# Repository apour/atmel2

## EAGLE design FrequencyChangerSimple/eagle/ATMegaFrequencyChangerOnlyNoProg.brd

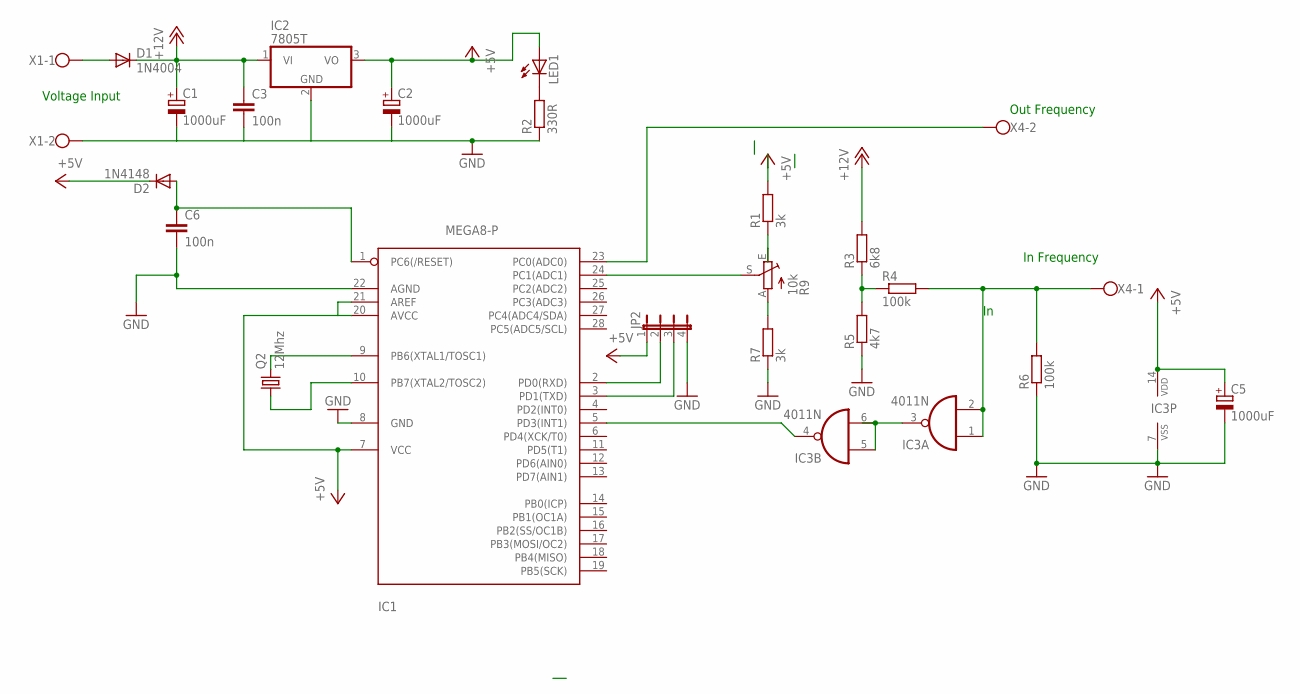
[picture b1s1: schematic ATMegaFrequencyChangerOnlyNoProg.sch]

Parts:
C1, C2, C5: 1000uF; E2,5-7
C3, C6: 100n; C025-024X044
D1: 1N4004; DO41-10
D2: 1N4148; DO35-10
IC1: MEGA8-P; DIL28-3
IC2: 7805T; TO220H
IC3: 4011N; DIL14
JP2: JP4E; JP4
LED1: LED5MM
Q2: 12Mhz; HC18U-V
R1, R7: 3k; 0207/10
R2: 330R; 0204/5
R3: 6k8; 0207/10
R4, R6: 100k; 0207/10
R5: 4k7; 0207/10
R9: 10k; RS3
X1, X4: W237-02P; W237-132

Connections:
+5V: C2.+, C5.+, D2.C, IC1.7 (VCC), IC1.20 (AVCC), IC1.21 (AREF), IC2.3 (VO), IC3.14 (VDD), JP2.1, LED1.A, R1.2
+12V: C1.+, C3.1, D1.C, IC2.1 (VI), R3.2
GND: C5.-, IC3.7 (VSS), R6.1
unnamed: D1.A, X1.1
unnamed: IC1.23 (PC0(ADC0)), X4.2
unnamed: IC1.5 (PD3(INT1)), IC3.4 (O)
unnamed: R3.1, R4.1, R5.2
unnamed: IC3.3 (O), IC3.5 (I0), IC3.6 (I1)
unnamed: R1.1, R9.E
unnamed: IC1.9 (PB6(XTAL1/TOSC1)), Q2.2
unnamed: R7.2, R9.A
unnamed: IC1.2 (PD0(RXD)), JP2.2
unnamed: IC1.24 (PC1(ADC1)), R9.S
unnamed: IC1.10 (PB7(XTAL2/TOSC2)), Q2.1
unnamed: IC1.3 (PD1(TXD)), JP2.3
unnamed: IC3.1 (I0), IC3.2 (I1), R4.2, R6.2, X4.1
unnamed: C1.-, C2.-, C3.2, C6.2, IC1.8 (GND), IC1.22 (AGND), IC2.2 (GND), JP2.4, R2.1, R5.1, R7.1, X1.2
unnamed: C6.1, D2.A, IC1.1 (PC6(/RESET))
unnamed: LED1.K (C), R2.2

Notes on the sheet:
Voltage Input
Out Frequency
In Frequency

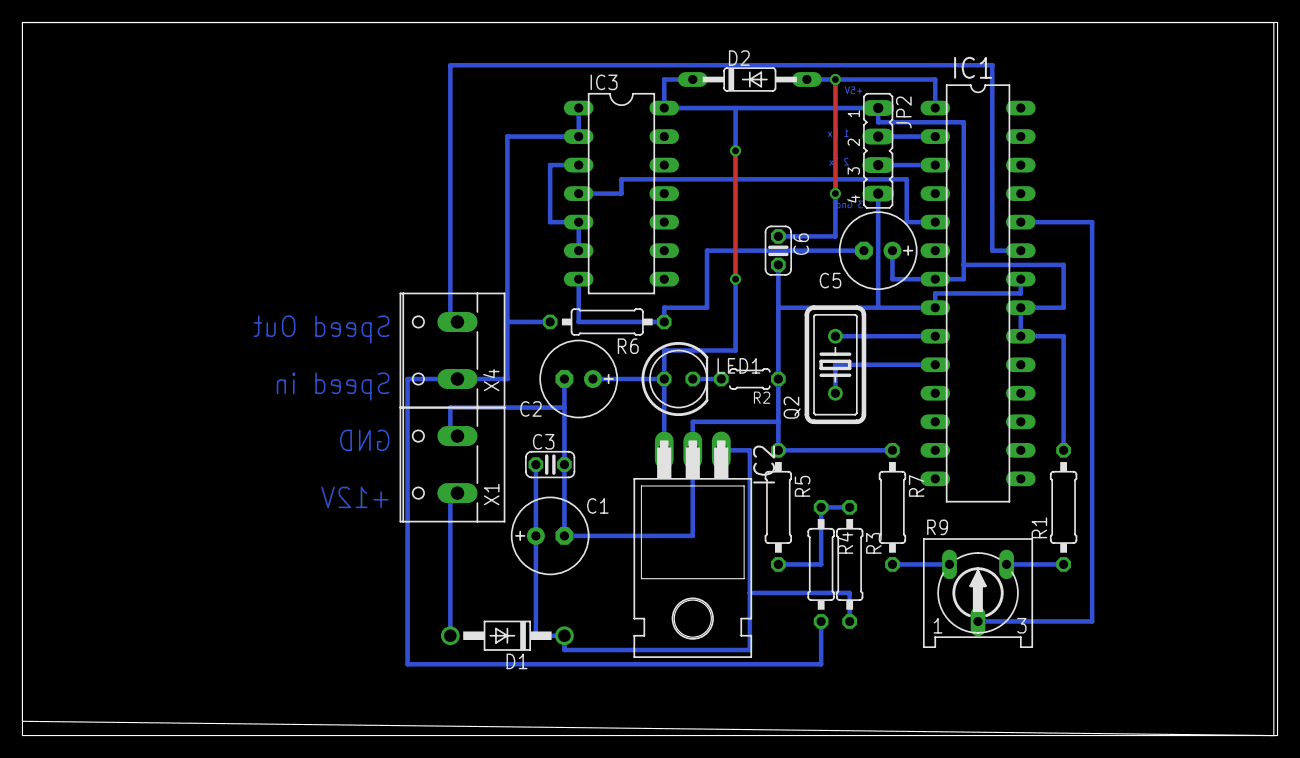
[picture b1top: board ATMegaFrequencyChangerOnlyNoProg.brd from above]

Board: 2 copper layers, 111.8 x 63.5 mm, 23 parts (0 on the bottom side), 19 nets.

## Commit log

2023-01-18 Tested in car Roman
2023-01-18 Scheme and board from eagle
2023-01-18 add projects
2023-02-27 add test file
2023-02-27 git commit 2
2023-03-07 Uprava pro spravnou detekci bez signalu. Rychlomer by nemel skocit na vyssi hodnoty, ale pouze se spravne vratit na 0.
2023-03-18 FrekvencyChanger simple - vyzkouseno
2023-03-18 Pokus slozitejsi algoritmus - nevyzkouseno
2023-03-20 Pouziti stavove machine pro detekci signalu
2023-03-21 Odzkouseno lokalne pouziti stavove machine
2023-03-25 Test filter input pulse length
2023-03-25 Vyzkouseno - po projizce
2023-03-29 Added new test file from new user
2023-03-29 S vypoctem minimalni delky signalu podle aktualni frekvence
2023-04-03 Test with check limit after every impulse
2023-04-05 Uart test example send with using interrupt
2023-04-05 Send to uart with interrupt
2023-04-10 essage for your changes. Lines starting Implement uart functions for UInt8, UInt16, UInt32
2023-04-10 Fixed warning in convert type uint8 pointer
2023-09-05 Spinani solaru
2023-09-05 Spinani Solaru s modem nabijeni
2023-09-20 Testing phase solar charge
2023-09-21 Odladeni simulaci, spinani ze site i ze solaru
2023-09-21 Odladeni spinani vetracku
2023-10-19 Pripraveno pro pouziti, simulace s define SIM_MEASURE
2023-10-20 Defines for PINS
2023-12-21 Had simple
2023-12-29 Support received interrupt
2024-01-01 Simple uart rx commands
2024-01-02 Command for limit added.
2024-01-02 Store limits in Eeprom.
2024-01-06 Uart send to separate file
2024-01-07 Add script for program fuses.
2024-02-11 Spinani solaru 2 - umi nacitat limit hodnotu pres uart
2024-02-11 Script for compile and program
2024-03-07 Add gitignore file
2024-03-07 After fix debug in AVR Studio
2024-03-07 Roman timer
2024-03-07 Simplify RomanTime code
2024-04-08 LPG Manager first commit Funguje vystup na nokia display port B, uart vystup port D 9200b
2024-04-12 Add machine state
2024-04-13 Implement start impuls on PIND7 Show running time on display
2024-05-14 Example use parallel digital input to serial input
2024-05-14 Read parallel data in uint16
2024-05-18 Zapis byte do Eprom asi funguje
2024-05-19 Eeprom funguje i cteni
2024-06-07 Set voltage with pcf8591
2024-09-22 Studna spinac kaloveho cerpadla
2024-09-22 Studna spinac projekt
2025-01-30 Spinac Redukce roman first test with timer
2025-01-30 Flash LED after found signal on INT0
2025-01-31 Tested on frequency 5Hz
2025-01-31 Adjusted on model
2025-02-05 Wire finder
2025-02-06 Nokia display test small
2025-02-06 Wire finder quick
2025-02-08 Testing LCD display port D - ATMega8
2025-02-13 Wire search frequency counter
2025-02-14 Use INT0 in at mega 8
2025-02-16 Show frequency on lcd display
2025-02-20 Update time for correct show frequency
2025-02-20 Add script for compile and program
2025-03-06 Work PORTC and PORTD
2025-03-06 Code cleanup
2025-09-03 Set Show LCD Static Text on port B
2025-09-05 Show frequency on PORTB display, input on INT0
2025-09-14 Pripsana detekce cisla kabelu
2025-09-20 Wire search tested
2026-02-11 Frequency changer with AI first tests
2026-02-22 test
2026-02-22 Frequency generator from Gemini AI - Measure on PD2 (INT0)
2026-02-26 Funguje nacitani frekvence z INT0, generovani stale frekvence z PB1
2026-02-27 Prenasi frekvenci OK od 39 Hz
2026-02-27 Funguje OK od 1-300 Hz
2026-03-04 ADC Example
2026-03-13 Frequency Generator works with ADC
2026-03-20 Read temp with DS18B20
2026-03-29 Read temperature with DS18B20, send result on UART 9600 baud, chip speed 10 Mhz
2026-03-29 Remove folder
2026-03-29 Read temperature on PB0, send result to UART, works OK
2026-03-29 Optimize code
2026-04-29 NetworkPing-SmartSockerViaTCP
2026-05-27 LED-D56 Show first 10 digits
2026-05-31 Counter from 0 to 99
2026-06-14 Add files via upload
    Read Network ping content file - ping to 192.168.1.130
2026-06-14 Add files via upload
    Network ping hex file - ping on 192.168.1.131 - response from www 192.168.1.131:80
